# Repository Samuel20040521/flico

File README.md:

# flico

**flico** = *flicker* + *pico*。

flico 是一台以 Raspberry Pi Pico 為核心、用來量測螢幕 / 光源閃爍(flicker)的小型自製
儀器。光訊號由 Vishay **BPW34** 矽 PIN 光二極體接收,經 Microchip **MCP6004** 跨阻
放大器(TIA)轉成電壓,由 Pico 的 ADC 取樣後,透過 USB-CDC 串列傳回桌面端的
**Rust GUI**(eframe + egui)即時繪出時域波形與 FFT 頻譜。

> 這個 repo 是專案的**線性故事版本**:每個 commit 大致對應一天的開發事件,
> 對應的研究日誌(`report/research-log/`)用敘事體把當天的決策、失敗、學到的東西
> 寫下來。雜亂的真實開發狀態收在另一個 repo(`SOC_Final/`)。

## 想做到什麼

把「看不見的閃」變成「看得見的曲線」。常見場景:

- **螢幕 PWM 調光的可見化**:筆電 / 手機 / 顯示器低亮度下的 \~200 Hz–25 kHz PWM 閃爍,
  用肉眼看不到,但會讓人疲勞、頭痛。
- **日光燈 / LED 燈具的 100 Hz / 120 Hz 漣波**:確認照明品質。
- **遮蔽測試**:用手指、紙片在 BPW34 前面晃動,即時看 ADC 訊號擺動,驗證整條訊號鏈。

最終目標是一台可以**單獨開機、自己看波形 + FFT** 的 handheld 儀器(目前 host GUI
跑在筆電上;3D 列印外殼還在進行中,見 `report/research-log/log.pdf` 結尾的「展望」)。

## 資料夾結構

| 資料夾 | 角色 | 主要技術棧 |
|---|---|---|
| [`firmware/`](firmware/) | 燒在 Pico 內的韌體 | Pico SDK C++、MicroPython(雙路線並存) |
| [`host/`](host/) | 桌面端 GUI,跟 Pico 通訊 | **Rust**(eframe + egui + egui\_plot),serialport |
| [`hardware/`](hardware/) | 三版 PCB 設計史 | KiCad 8 + SKiDL(中間版)+ JLCPCB |
| [`mechanical/`](mechanical/) | 3D 列印外殼(進行中) | Fusion 360 Python API |
| [`simulation/`](simulation/) | PySpice TIA 模擬與量測對照 | Python(uv)、PySpice、ngspice |
| [`report/research-log/`](report/research-log/) | 每日研究日誌 + Gemini 對話原檔 | XeLaTeX(xeCJK + TW-Kai)、biblatex+biber |

### `firmware/` 內部

| 子資料夾 | 內容 |
|---|---|
| `cpp-version/` | **主要韌體**:Pico SDK C++,含 SSD1306 OLED 驅動 + ADC + USB-CDC 串流(5/12 從 MicroPython fork 過來) |
| `python-version/` | MicroPython 版主程式(歷史路線,5/8 \~ 5/11 用) |
| `led-light-test-cpp-version/` | C++ blink,Pico SDK 工具鏈試水溫 |
| `led-light-test-python-version/` | MicroPython blink,VS Code 環境驗證(5/8) |

### `hardware/` 內部(三版線性史)

| 子資料夾 | 內容 | 狀態 |
|---|---|---|
| `first-version/` | `pico_flicker_shield` —— 5/8 KiCad GUI workflow 起手,schematic 完成 | 放棄,留作設計史 |
| `second-version/` | `PD_detector_pro` —— 5/18 用 SKiDL 程式化重寫 + pcbnew API 自動 layout | 放棄,但 flipped analog island 的領悟帶到 final |
| `final-version/` | `SOC_Final` —— 5/20\~5/25 投產版,5/25 21:23 送 JLCPCB | **已送 PCBA** |

`final-version/` 內有 `Gerber/`(14 個製造檔)、`SOC_Final_JLCPCB.zip`(36 KB 一鍵上傳包)、
`TIA_Gain_100M.wbk`(KiCad spice 工作簿)、`tools/jlcpcb_bom_cpl.py`(BOM/CPL 生成腳本)。

## 如何在本地跑通過程

各子資料夾互不耦合,看你想做什麼進對應資料夾即可。

### 1. 桌面 GUI(`host/`)

```sh
cd host
cargo run --release                # 接實體 Pico,從 USB-CDC 拉資料
cargo run --release -- --synth     # 用合成正弦+雜訊跑 demo(不用接 Pico)
```

- macOS 會自動掃 `/dev/cu.usbmodem*`;Windows 預設 `COM3`(已知 Pico 第一次插的位置)。
- 也可以 build 成 WASM,丟瀏覽器跑:

  ```sh
  cargo build --release --target wasm32-unknown-unknown
  ```

- 跨平台 release binary(macOS universal + Windows x86\_64)透過 GitHub Actions
  `.github/workflows/release-rust_flico.yml` 在 push tag 時自動 cross-compile。

### 2. 韌體(`firmware/cpp-version/`)

```sh
cd firmware/cpp-version
mkdir -p build && cd build
cmake .. && make -j$(nproc)
# 產出 pico_flicker.uf2,把 Pico 用 BOOTSEL 鍵插上拖進 RPI-RP2 磁碟即可
```

需要 [Pico SDK](https://github.com/raspberrypi/pico-sdk) 並設好 `PICO_SDK_PATH`
環境變數。

> 想用 MicroPython 路線跑舊版的話,在 VS Code 裝 MicroPython 擴充,
> 把 `firmware/python-version/{main.py,ssd1306.py}` 上傳到 Pico 即可。

### 3. PySpice 模擬(`simulation/`)

```sh
cd simulation
uv sync                              # 安裝 Python 相依
uv run python main.py                # DC sweep → figures/tia_sweep.png
uv run python ac_transient_sweep.py  # AC Bode + 20 kHz PWM transient
```

需要先有 `libngspice0`(Linux,`apt install libngspice0-dev`)或
`ngspice`(macOS:`brew install ngspice`)。詳見 [`simulation/report.md`](simulation/report.md)。

把實測噪音餵 spice 的 pipeline:

```sh
cd host
uv run python convert.py             # flicker_*.csv → kicad_noise_pwl.txt
# 把 kicad_noise_pwl.txt 路徑塞進 final-version/TIA_Gain_100M.wbk 的 PWL source
```

### 4. PCB(`hardware/final-version/`)

用 [KiCad 8.0](https://www.kicad.org/) 打開 `SOC_Final.kicad_pro`。

- 看 ERC 結果:`ERC.rpt`
- 看完整投產包:`SOC_Final_JLCPCB.zip`
- 重新生 BOM/CPL:

  ```sh
  cd hardware/final-version
  python tools/jlcpcb_bom_cpl.py
  ```

> KiCad project stem 刻意保留為 `SOC_Final`(repo 名雖然是 flico,但 KiCad internal
> cross-references 跟 stem 綁死,改 stem blast radius 太大)。

### 5. 3D 列印外殼(`mechanical/`,進行中)

在 Fusion 360 → **Scripts and Add-Ins** → **+** → 指到
`mechanical/fusion_pico_fixture.py`,跑一次就會 parametrically 生出 fixture 模型。
參數(housing 60 × 30 × 20 mm 等)集中在檔頭常數區。

目前還是 fixture 級別的 stub,**不是整機 enclosure**。升級計畫見研究日誌結尾的
「展望」section。

### 6. 研究日誌(`report/research-log/`)

```sh
cd report/research-log
xelatex log.tex && biber log && xelatex log.tex && xelatex log.tex
open log.pdf
```

需要 TW-Kai(全字庫正楷體)字型,可從
[CNS11643 下載頁](https://www.cns11643.gov.tw/opendata/Fonts_Kai.zip)取得。

寫新 entry 的工作流:

1. 新增 `entries/YYYY-MM-DD.tex`(每日一檔)
2. 圖 / 影片放 `figures/YYYY-MM-DD/`
3. 原始 Gemini 對話放 `gemini_discuss_history/MMDD[-suffix].txt`
4. 在 `log.tex` 條目區追加:

   ```latex
   \logentry{YYYY-MM-DD}{當日標題}
   \input{entries/YYYY-MM-DD}
   ```

5. 重新編譯。

## 設計細節

電路拓樸、`R_F` / `C_F` 選擇邏輯、量測 vs 模擬對照,看
[`simulation/report.md`](simulation/report.md)。

PCB 三版的決策史、host 從 Python 改寫到 Rust 的效能對照、JLCPCB 投產的務實妥協,
看研究日誌(`report/research-log/log.pdf`)。

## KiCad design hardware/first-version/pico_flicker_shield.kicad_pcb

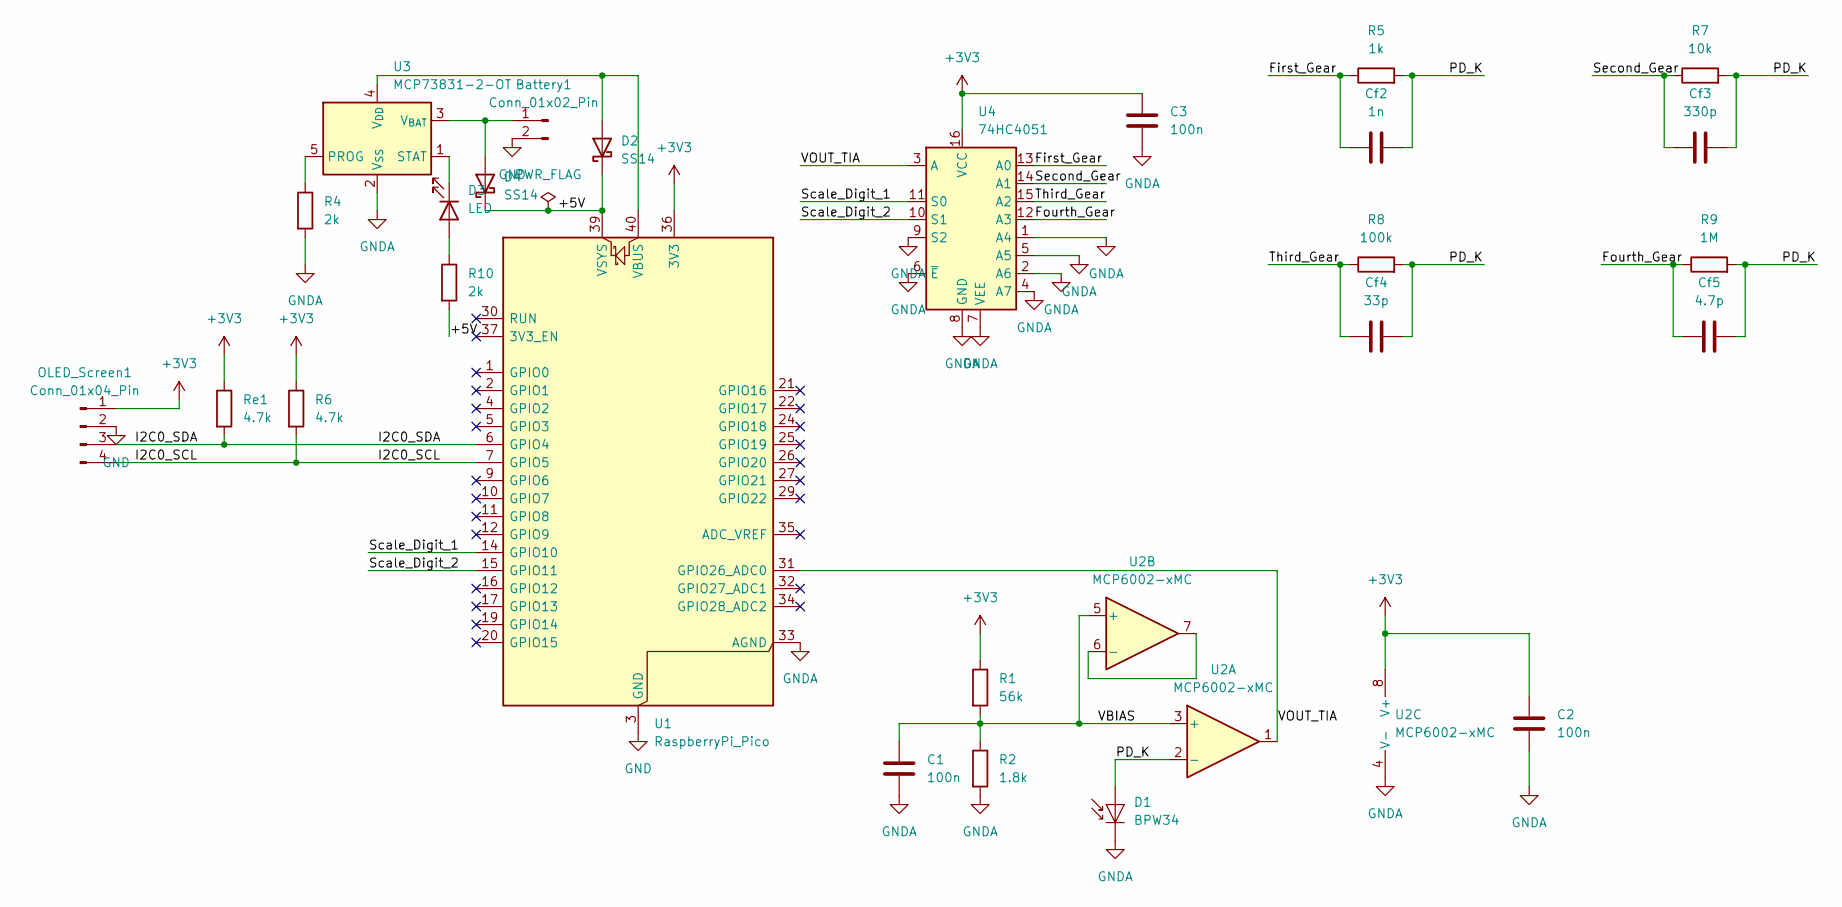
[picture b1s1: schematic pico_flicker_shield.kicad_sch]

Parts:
Battery1: Conn_01x02_Pin
C1, C3: 100n; C_0805_2012Metric; LCSC C49645
C2: 100n; C_0805_2012Metric
Cf2: 1n; C_0805_2012Metric
Cf3: 330p; C_0805_2012Metric
Cf4: 33p; C_0805_2012Metric
Cf5: 4.7p; C_0805_2012Metric
D1: BPW34; Osram_DIL2_4.3x4.65mm_P5.08mm
D2, D4: SS14; D_SMA
D3: LED; LED_0805_2012Metric
OLED_Screen1: Conn_01x04_Pin; PinHeader_1x04_P2.54mm_Vertical
R1: 56k; R_0805_2012Metric; LCSC C17414
R2: 1.8k; R_0805_2012Metric
R4, R10: 2k; R_0805_2012Metric; LCSC C17414
R5: 1k; R_0805_2012Metric
R6: 4.7k; R_0805_2012Metric; LCSC C17630
R7: 10k; R_0805_2012Metric
R8: 100k; R_0805_2012Metric
R9: 1M; R_0805_2012Metric
Re1: 4.7k; R_0805_2012Metric; LCSC C17630
U1: RaspberryPi_Pico; RaspberryPi_Pico_Common_THT
U2: MCP6002-xMC; MSOP-8_3x3mm_P0.65mm
U3: MCP73831-2-OT; SOT-23-5
U4: 74HC4051; SOIC-16_3.9x9.9mm_P1.27mm

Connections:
+3V3: C2.1, C3.1, OLED_Screen1.1, R1.1, R6.1, Re1.1, U1.36 (3V3), U2.8 (V+), U4.16 (VCC)
/+5V: D2.1 (K), D4.1 (K), R10.2, U1.39 (VSYS)
/First_Gear: Cf2.1, R5.1, U4.13 (A0)
/Fourth_Gear: Cf5.1, R9.1, U4.12 (A3)
/I2C0_SCL: OLED_Screen1.4, R6.2, U1.7 (GPIO5)
/I2C0_SDA: OLED_Screen1.3, Re1.2, U1.6 (GPIO4)
/PD_K: Cf2.2, Cf3.2, Cf4.2, Cf5.2, D1.2 (A), R5.2, R7.2, R8.2, R9.2, U2.2 (-)
/Scale_Digit_1: U1.14 (GPIO10), U4.11 (S0)
/Scale_Digit_2: U1.15 (GPIO11), U4.10 (S1)
/Second_Gear: Cf3.1, R7.1, U4.14 (A1)
/Third_Gear: Cf4.1, R8.1, U4.15 (A2)
/VBIAS: C1.1, R1.2, R2.1, U2.3 (+), U2.5 (+)
/VOUT_TIA: U1.31 (GPIO26_ADC0), U2.1, U4.3 (A)
GND: Battery1.2, OLED_Screen1.2, U1.3 (GND), U1.8 (GND), U1.13 (GND), U1.18 (GND), U1.23 (GND), U1.28 (GND), U1.38 (GND)
GNDA: C1.2, C2.2, C3.2, D1.1 (K), R2.2, R4.2, U1.33 (AGND), U2.4 (V-), U2.9 (V-), U3.2 (V_{SS}), U4.1 (A4), U4.2 (A6), U4.4 (A7), U4.5 (A5), U4.6 (~E), U4.7 (VEE), U4.8 (GND), U4.9 (S2)
unnamed: Battery1.1, D4.2 (A), U3.3 (V_{BAT})
unnamed: D2.2 (A), U1.40 (VBUS), U3.4 (V_{DD})
unnamed: D3.2 (A), R10.1
unnamed: D3.1 (K), U3.1 (STAT)
unnamed: U2.6 (-), U2.7
unnamed: R4.1, U3.5 (PROG)

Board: 2 copper layers, 26 parts (0 on the bottom side), 21 nets, no tracks yet.

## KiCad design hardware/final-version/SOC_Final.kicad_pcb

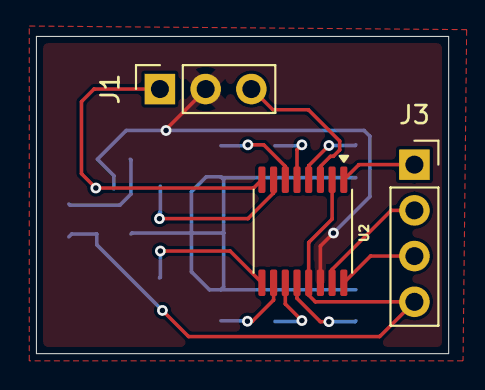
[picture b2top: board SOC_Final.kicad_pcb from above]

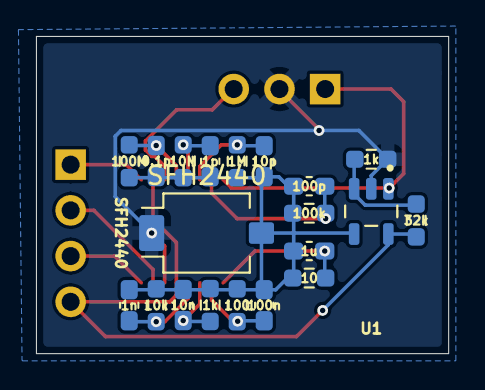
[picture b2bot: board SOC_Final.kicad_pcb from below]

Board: 2 copper layers, 22.9 x 17.6 mm, 23 parts (20 on the bottom side), 17 nets.

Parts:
C1: 0.1p; C_0603_1608Metric_Pad1.08x0.95mm_HandSolder
C2: 1p; C_0603_1608Metric_Pad1.08x0.95mm_HandSolder
C3: 10p; C_0603_1608Metric_Pad1.08x0.95mm_HandSolder
C4: 100p; C_0603_1608Metric_Pad1.08x0.95mm_HandSolder
C5: 1n; C_0603_1608Metric_Pad1.08x0.95mm_HandSolder
C6: 10n; C_0603_1608Metric_Pad1.08x0.95mm_HandSolder
C7: 100n; C_0603_1608Metric_Pad1.08x0.95mm_HandSolder
C8: 1u; C_0603_1608Metric_Pad1.08x0.95mm_HandSolder
J1: Conn_01x03_Socket; PinSocket_1x03_P2.54mm_Vertical
J3: Conn_01x04_Socket; PinSocket_1x04_P2.54mm_Vertical
R1: 100M; R_0603_1608Metric_Pad0.98x0.95mm_HandSolder
R2, R8: 1k; R_0603_1608Metric_Pad0.98x0.95mm_HandSolder
R3: 32k; R_0603_1608Metric_Pad0.98x0.95mm_HandSolder
R4: 10M; R_0603_1608Metric_Pad0.98x0.95mm_HandSolder
R5: 1M; R_0603_1608Metric_Pad0.98x0.95mm_HandSolder
R6: 100k; R_0603_1608Metric_Pad0.98x0.95mm_HandSolder
R7: 10k; R_0603_1608Metric_Pad0.98x0.95mm_HandSolder
R9: 100; R_0603_1608Metric_Pad0.98x0.95mm_HandSolder
R10: 10; R_0603_1608Metric_Pad0.98x0.95mm_HandSolder
SFH2440: SFH2440; Osram_SFH2440
U1: OPA320AIDBVR; SOT95P280X145-5N
U2: TMUX1208PW; TSSOP-16_4.4x5mm_P0.65mm

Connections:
0: J1.3, U2.3 (VSS)
/+3V3: J3.4, R3.2, U1.5 (V+), U2.2 (EN), U2.13 (VDD)
/GEAR1: C1.1, R1.1, U2.4 (S1)
/GEAR2: C2.1, R4.1, U2.5 (S2)
/GEAR3: C3.1, R5.1, U2.6 (S3)
/GEAR4: C4.1, R6.1, U2.7 (S4)
/GEAR5: C5.1, R7.1, U2.12 (S5)
/GEAR6: C6.1, R8.1, U2.11 (S6)
/GEAR7: C7.1, R9.1, U2.10 (S7)
/GEAR8: C8.1, R10.1, U2.9 (S8)
/GND_A: J1.2, R2.1, SFH2440.1 (K), U1.2 (V-), U2.14 (GND)
/MUX_A0: J3.1, U2.1 (A0)
/MUX_A1: J3.3, U2.16 (A1)
/MUX_A2: J3.2, U2.15 (A2)
/TIA_OUT: J1.1, U1.1 (OUT), U2.8 (D)
/TIA_SUM: C1.2, C2.2, C3.2, C4.2, C5.2, C6.2, C7.2, C8.2, R1.2, R4.2, R5.2, R6.2, R7.2, R8.2, R9.2, R10.2, SFH2440.2 (A), U1.4 (-IN)
/V_REF: R2.2, R3.1, U1.3 (+IN)

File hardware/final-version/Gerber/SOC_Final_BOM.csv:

Comment,Designator,Footprint,Quantity,Description,LCSC
0.1p,C1,Capacitor_SMD:C_0603_1608Metric_Pad1.08x0.95mm_HandSolder,1,Capacitor 0.1p 0603,
1p,C2,Capacitor_SMD:C_0603_1608Metric_Pad1.08x0.95mm_HandSolder,1,Capacitor 1p 0603,
10p,C3,Capacitor_SMD:C_0603_1608Metric_Pad1.08x0.95mm_HandSolder,1,Capacitor 10p 0603,
100p,C4,Capacitor_SMD:C_0603_1608Metric_Pad1.08x0.95mm_HandSolder,1,Capacitor 100p 0603,
1n,C5,Capacitor_SMD:C_0603_1608Metric_Pad1.08x0.95mm_HandSolder,1,Capacitor 1n 0603,
10n,C6,Capacitor_SMD:C_0603_1608Metric_Pad1.08x0.95mm_HandSolder,1,Capacitor 10n 0603,
100n,C7,Capacitor_SMD:C_0603_1608Metric_Pad1.08x0.95mm_HandSolder,1,Capacitor 100n 0603,
1u,C8,Capacitor_SMD:C_0603_1608Metric_Pad1.08x0.95mm_HandSolder,1,Capacitor 1u 0603,
Conn_01x03_Socket,J1,Connector_PinSocket_2.54mm:PinSocket_1x03_P2.54mm_Vertical,1,Pin header/socket,
Conn_01x04_Socket,J3,Connector_PinSocket_2.54mm:PinSocket_1x04_P2.54mm_Vertical,1,Pin header/socket,
100M,R1,Resistor_SMD:R_0603_1608Metric_Pad0.98x0.95mm_HandSolder,1,Resistor 100M 0603,
1k,"R2,R8",Resistor_SMD:R_0603_1608Metric_Pad0.98x0.95mm_HandSolder,2,Resistor 1k 0603,
32k,R3,Resistor_SMD:R_0603_1608Metric_Pad0.98x0.95mm_HandSolder,1,Resistor 32k 0603,
10M,R4,Resistor_SMD:R_0603_1608Metric_Pad0.98x0.95mm_HandSolder,1,Resistor 10M 0603,
1M,R5,Resistor_SMD:R_0603_1608Metric_Pad0.98x0.95mm_HandSolder,1,Resistor 1M 0603,
100k,R6,Resistor_SMD:R_0603_1608Metric_Pad0.98x0.95mm_HandSolder,1,Resistor 100k 0603,
10k,R7,Resistor_SMD:R_0603_1608Metric_Pad0.98x0.95mm_HandSolder,1,Resistor 10k 0603,
100,R9,Resistor_SMD:R_0603_1608Metric_Pad0.98x0.95mm_HandSolder,1,Resistor 100 0603,
10,R10,Resistor_SMD:R_0603_1608Metric_Pad0.98x0.95mm_HandSolder,1,Resistor 10 0603,
SFH2440,SFH2440,OptoDevice:Osram_SFH2440,1,SFH2440,
OPA320AIDBVR,U1,OPA320AIDBVR:SOT95P280X145-5N,1,IC OPA320AIDBVR,
TMUX1208PW,U2,Package_SO:TSSOP-16_4.4x5mm_P0.65mm,1,IC TMUX1208PW,

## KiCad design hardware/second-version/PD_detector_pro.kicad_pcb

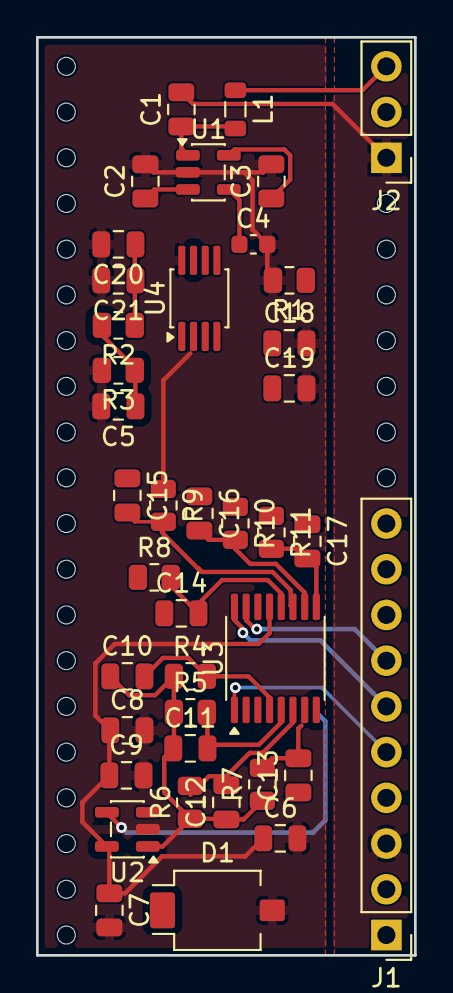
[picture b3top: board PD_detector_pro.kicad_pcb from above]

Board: 2 copper layers, 21.0 x 51.0 mm, 41 parts (0 on the bottom side), 24 nets.

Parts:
C1, C2, C3: 1uF; C_0805_2012Metric
C4: 10nF; C_0603_1608Metric
C5, C6, C8, C18, C20: 100nF; C_0805_2012Metric
C7, C9, C19, C21: 10uF; C_0805_2012Metric
C10: 10nF; C_0805_2012Metric
C11: 3.3nF; C_0805_2012Metric
C12: 1nF; C_0805_2012Metric
C13: 330pF; C_0805_2012Metric
C14: 100pF; C_0805_2012Metric
C15: 33pF; C_0805_2012Metric
C16: 10pF; C_0805_2012Metric
C17: DNP; C_0805_2012Metric
D1: SFH2440; Osram_SFH2440
J1: Conn_01x10; PinHeader_1x10_P2.54mm_Vertical
J2: Conn_01x03; PinHeader_1x03_P2.54mm_Vertical
L1: 600R@100MHz; L_0805_2012Metric
PICO_PINS: Pico_thru
R1: 0; R_0805_2012Metric
R2, R8: 100k; R_0805_2012Metric
R3: 4.7k; R_0805_2012Metric
R4: 1k; R_0805_2012Metric
R5: 3.3k; R_0805_2012Metric
R6: 10k; R_0805_2012Metric
R7: 33k; R_0805_2012Metric
R9: 330k; R_0805_2012Metric
R10: 1M; R_0805_2012Metric
R11: 10M; R_0805_2012Metric
U1: LP5907MFX-3.3; SOT-23-5
U2: OPA320AIDBVR; SOT-23-5
U3: TMUX1208PWR; TSSOP-16_4.4x5mm_P0.65mm
U4: ADS8326; MSOP-8_3x3mm_P0.65mm

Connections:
+3V3_A: C3.1, C6.1, C7.1, C8.1, C9.1, C18.1, C19.1, C20.1, C21.1, R2.1, U1.5, U2.5, U3.13, U4.1, U4.8
GEAR0: C10.2, R4.2, U3.4
GEAR1: C11.2, R5.2, U3.5
GEAR2: C12.2, R6.2, U3.6
GEAR3: C13.2, R7.2, U3.7
GEAR4: C14.2, R8.2, U3.12
GEAR5: C15.2, R9.2, U3.11
GEAR6: C16.2, R10.2, U3.10
GEAR7: C17.2, R11.2, U3.9
GND: C1.2, J1.3, J2.1, R1.1
GNDA: C2.2, C3.2, C4.2, C5.2, C6.2, C7.2, C8.2, C9.2, C18.2, C19.2, C20.2, C21.2, D1.2, R1.2, R3.2, U1.2, U2.2, U3.14, U4.4
LDO_BYP: C4.1, U1.4
MUX_A0: J1.5, U3.1
MUX_A1: J1.6, U3.16
MUX_A2: J1.7, U3.15
MUX_EN: J1.8, U3.2
SPI_CS: J1.2, U4.5
SPI_SCK: J1.4, U4.7
SPI_SDO: J1.1, U4.6
TIA_OUT: C10.1, C11.1, C12.1, C13.1, C14.1, C15.1, C16.1, C17.1, R4.1, R5.1, R6.1, R7.1, R8.1, R9.1, R10.1, R11.1, U2.1, U4.2
TIA_SUM: D1.1, U2.4, U3.8
VBUS: J2.3, L1.1
VBUS_FILT: C1.1, C2.1, L1.2, U1.1, U1.3
V_REF: C5.1, R2.2, R3.1, U2.3, U4.3

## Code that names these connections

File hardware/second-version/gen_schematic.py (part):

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# ----------------------------------------------------------------------------
J_SIG = Part("Connector_Generic", "Conn_01x10",
             footprint="Connector_PinHeader_2.54mm:PinHeader_1x10_P2.54mm_Vertical")
J_SIG[1]  += spi_sdo     # Pico pin 21 = GP16 (SPI0 RX / MISO)
J_SIG[2]  += spi_cs      # Pico pin 22 = GP17
J_SIG[3]  += gnd         # Pico pin 23 = GND
J_SIG[4]  += spi_sck     # Pico pin 24 = GP18 (SPI0 SCK)
J_SIG[5]  += mux_a0      # Pico pin 25 = GP19  <-- was GP10
J_SIG[6]  += mux_a1      # Pico pin 26 = GP20  <-- was GP11
J_SIG[7]  += mux_a2      # Pico pin 27 = GP21  <-- was GP12
J_SIG[8]  += mux_en      # Pico pin 28 = GP22  <-- was GP13
# J_SIG[9]  = Pico pin 29 = RUN  -- LEAVE NC! Connecting would reset the Pico
# J_SIG[10] = Pico pin 30 = GP26 -- NC (reserved for future ADC0 use)

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
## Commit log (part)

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2026-06-07 Add 2026-05-20 entry: final PCB (SOC_Final) — design, simulation, JLCPCB submission on 5/25
    5/20 was the kickoff of the third and final PCB attempt that ran for
    six days. The entry covers the entire arc from blank schematic to
    JLCPCB submission, including the parallel host/ UI/UX iteration.
    Day-by-day:
    - Day 1 (5/20): blank schematic → first ERC run at 15:53 (ERC.rpt
    timestamp). Wrote tools/silkscreen_normalize.py to bulk-format
2026-06-07 Add 2026-05-18 entry: design first-version PCB (PD_detector_pro)
    5/18 was a full-day PCB layout session in KiCad. Goal was *not* to
    ship a board to JLCPCB — too many specs (sensor choice, battery
    inclusion, ADC software chain) hadn't converged yet. Goal was to:
    1) get the SKiDL → KiCad netlist → pcbnew Python API pipeline working
    2) survey what the breadboard-grade parts (MCP6002 + 74HC4051 + Pico ADC)
    would look like if upgraded to lab-grade (OPA328 + TMUX1208 + ADS8326)
2026-06-07 Rename PD_detector_pro to second-version; add pico_flicker_shield as the real first-version
    The previous 5/18 commit named PD_detector_pro 'first-version' — that
    was wrong. The actual first PCB attempt was pico_flicker_shield,
    started in KiCad on 2026-05-08 right after the MicroPython signal
    chain came online. It used the traditional KiCad GUI workflow
    (Schematic Editor → Footprint Assignment → PCB Editor) and ran for
    ~10 days of intermittent edits before being abandoned on 5/18 in
2026-06-07 Add 2026-05-19 entry: rewrite host/ from Python (matplotlib → PyQtGraph) to Rust
    5/19 documents the host-side plotting story arc that ran from 5/8 to today:
    1. matplotlib + plt.ion() (5/8–5/12): worked for the first signal-chain
    bringup but flickered on macOS retina — backend redraws desync from
    60Hz V-sync. Capped at ~20 fps even with tiny windows.
    2. PyQtGraph + OpenGL (5/13–5/18): solved the flicker (Qt double-buffering
    + V-sync) but hit an architectural ceiling at ~3e4 accumulated samples —
2026-06-07 Add host/ Rust GUI crate (rust_flico): companion to 2026-05-19 entry
    The 5/19 entry documents abandoning Python (matplotlib → PyQtGraph) for
    Rust + eframe/egui due to performance ceilings beyond 3×10^4 samples.
    This commit lands the actual Rust code referenced by that entry.
    Layout:
    - host/Cargo.toml — crate manifest (crate name stays `rust_flico`;
    CLAUDE.md explains the kept name vs the new
2026-06-07 Add host/convert.py + measured-noise PWL + 4 baseline CSVs: companion to 2026-05-20 entry
    The 5/20 entry calls the "measured CSV → PWL → KiCad spice" pipeline
    the proudest methodology of the project — but the actual files were
    still in SOC_Final/host/. This commit lands them next to the Rust GUI:
    - host/convert.py — pandas script that reads a host/-exported
    flicker_*.csv and emits a KiCad-compatible
    PWL noise source (kicad_noise_pwl.txt).
2026-06-07 Add release-rust_flico CI workflow
    GitHub Actions workflow that cross-compiles the host/ Rust GUI and
    publishes release binaries on tag push:
    - macOS universal binary (x86_64 + aarch64 lipo'd together).
    - Windows x86_64 binary.
    The 5/19 entry's 下一步 ④ explicitly tags this CI as "to be done the
    next day (5/20)" — landing it here as a logical companion to that arc.
2026-06-07 Add mechanical/ stubs + 展望 section: future-work response to maker spirit
    老師第二堂課鼓勵「自己畫 PCB、自己 3D 列印」的創客精神 — PCB 那條線
    三版已走完(first/second/final-version + JLCPCB 投產),3D 列印這條
    線還在學,但起手已經對齊。本 commit 把進行中的 mechanical/ 起手
    產出搬入,並在 log.tex 末尾加上「展望」section 把這條線講清楚。
    mechanical/ 內容(stub 級別,不是成品):
    - fusion_pico_fixture.py — Fusion 360 嵌入式 Python script,
2026-06-07 Add CLAUDE.md: handoff doc for next Claude session
    flico-fresh 是 SOC_Final 的線性故事版,內容已逐步補齊到 4/19→展望
    完整時間軸。本檔給下一個 Claude session 用:
    - 兩個 repo 角色對映表(flico-fresh = 給人看 / SOC_Final = 真正幹活)
    - 子資料夾 → SOC_Final 對映,方便未來補檔知道去哪撈
    - 寫研究日誌的模板(\logentry + entries/ + figures/ + 編譯流程)
    - 跨資料夾耦合圖
2026-06-07 Add README.md: project intro + folder map + local run instructions
    flico-fresh 的對外門面。從 SOC_Final/README.md 的骨架改寫,反映新結構:
    - 三版 hardware/{first,second,final}-version 線性史(取代原本的 main_board/
    shield 平行分類)
    - firmware 雙路線:cpp-version(主要)/ python-version(歷史)+ 兩個 led-light-test
    - host 改成 Rust(eframe + egui)而非舊 Python pyserial 描述
    - mechanical/ 標示為「進行中」,呼應 log.pdf 結尾的展望 section
2026-06-07 Add report/main.tex: flico 期末主報告(麵包板版現況 + PCB 版未來展望)
    10 頁的 XeLaTeX 主報告,跟 research-log 同套排版(TW-Kai + AutoFakeBold)。
    跟 research-log 是「敘事體姊妹篇」的關係 — research-log 寫每天的事件流,
    main.tex 寫「裝置作為一個系統的最終樣貌」。
    內容大綱:
    - §1 前言:為什麼要量「看不見的閃」(IEEE 1789 動機 + 4 個設計目標)
    - §2 系統概觀:5 級訊號鏈 + BOM 表
2026-06-07 Update CLAUDE.md: mark D (main.tex) done
